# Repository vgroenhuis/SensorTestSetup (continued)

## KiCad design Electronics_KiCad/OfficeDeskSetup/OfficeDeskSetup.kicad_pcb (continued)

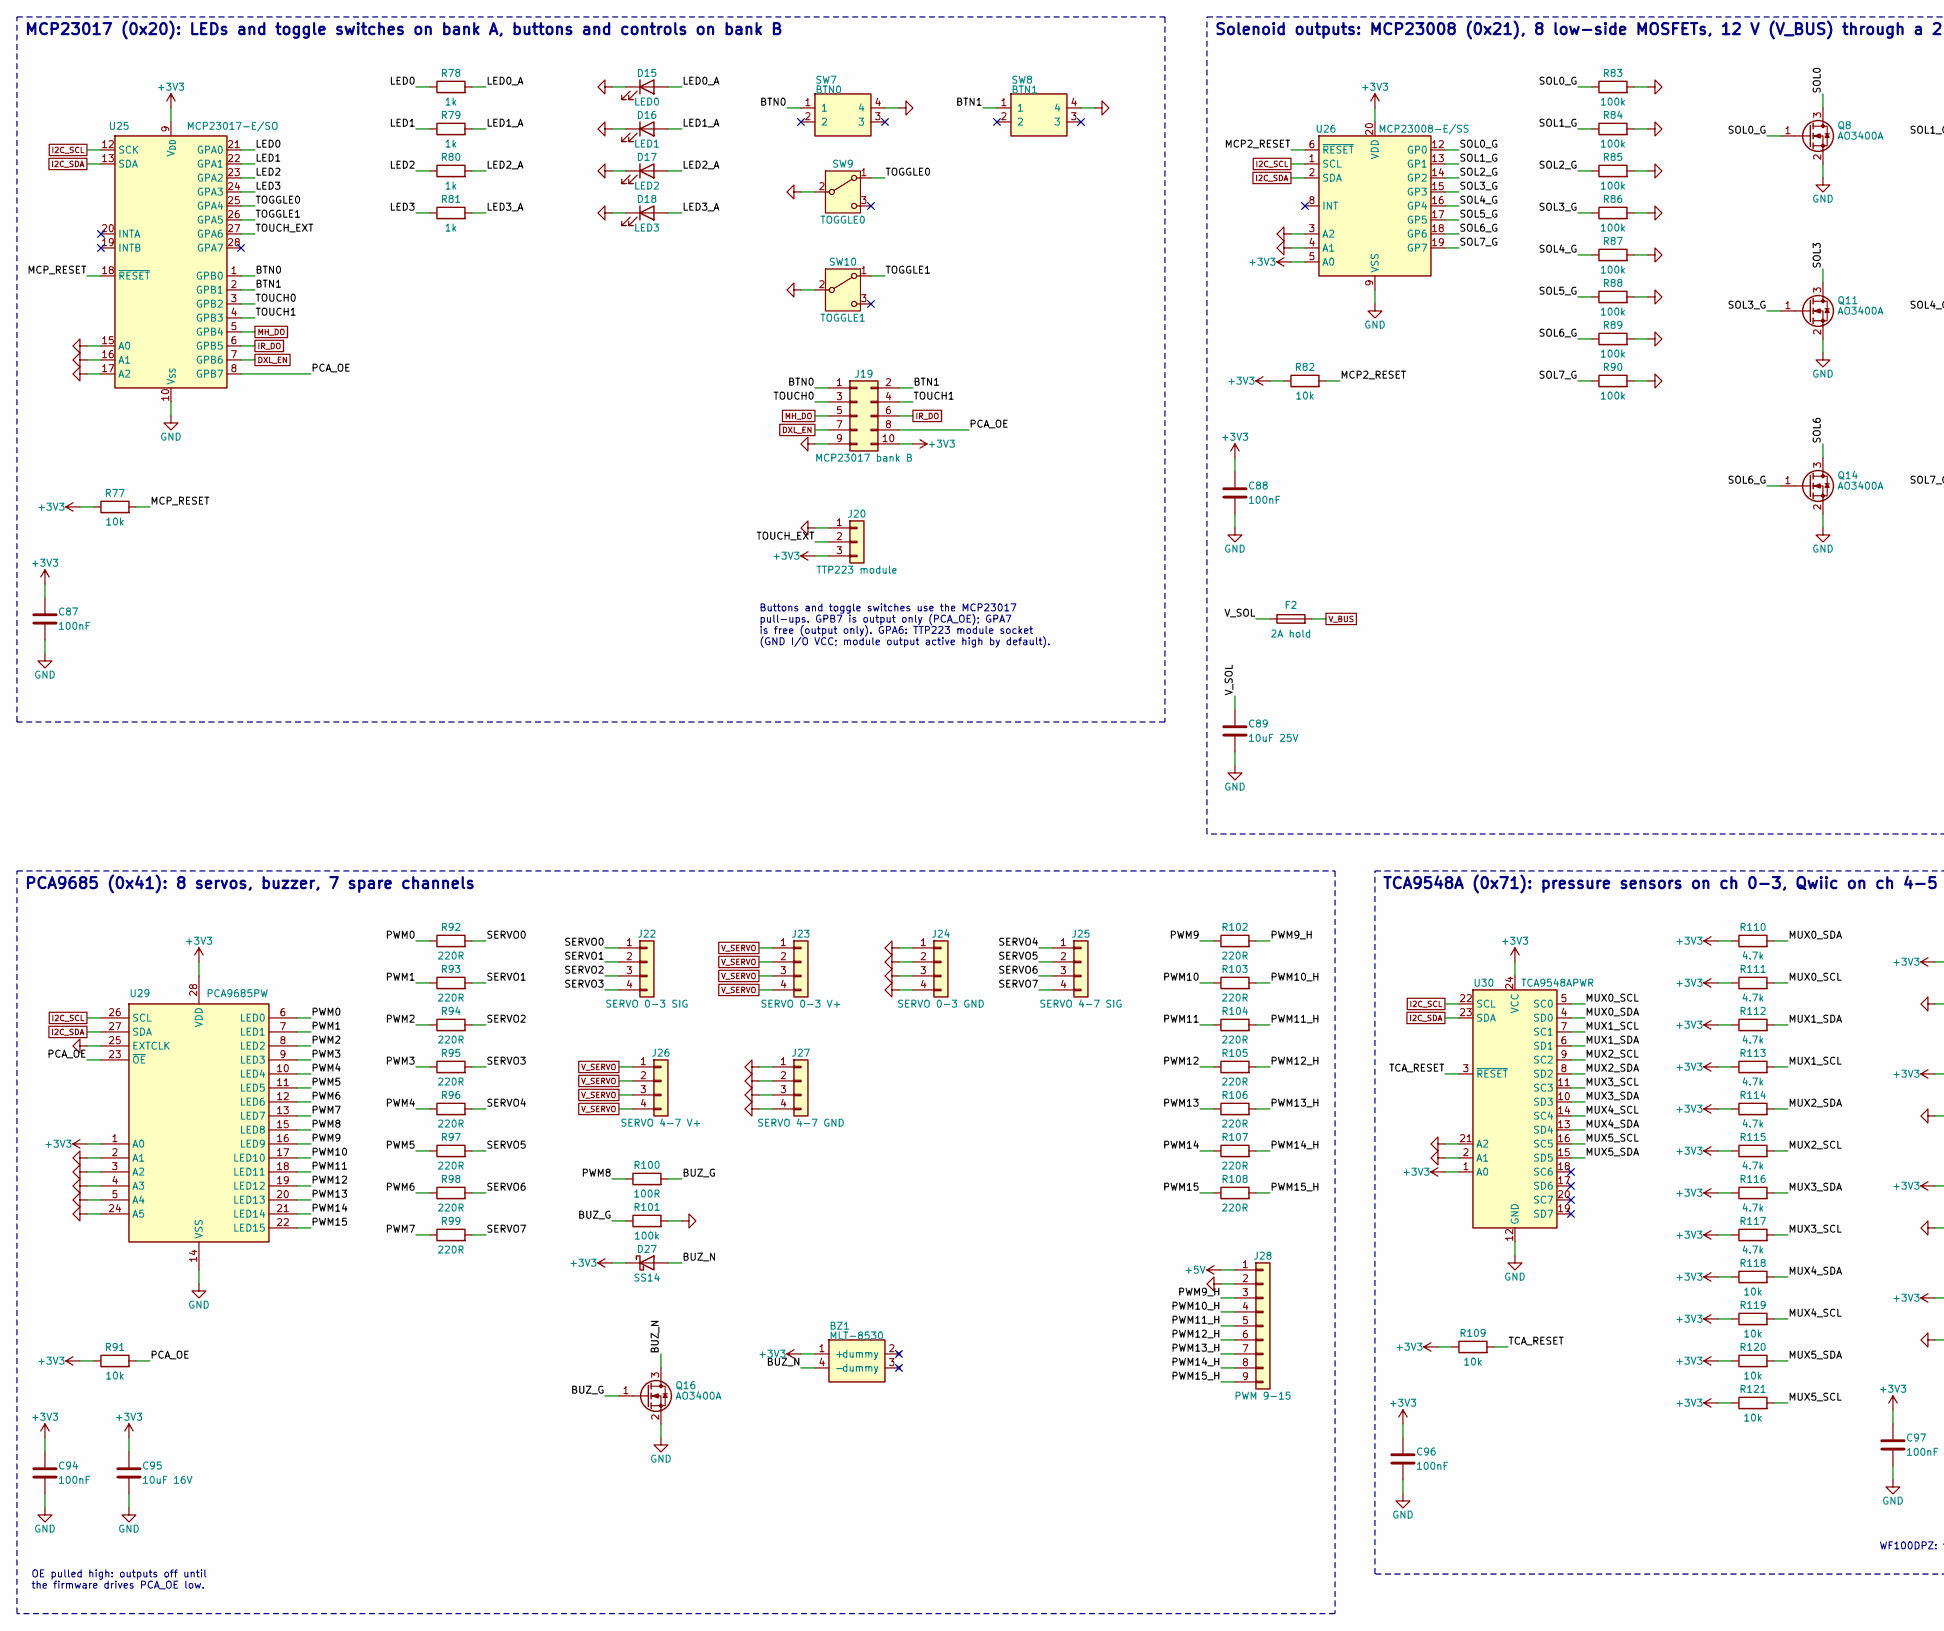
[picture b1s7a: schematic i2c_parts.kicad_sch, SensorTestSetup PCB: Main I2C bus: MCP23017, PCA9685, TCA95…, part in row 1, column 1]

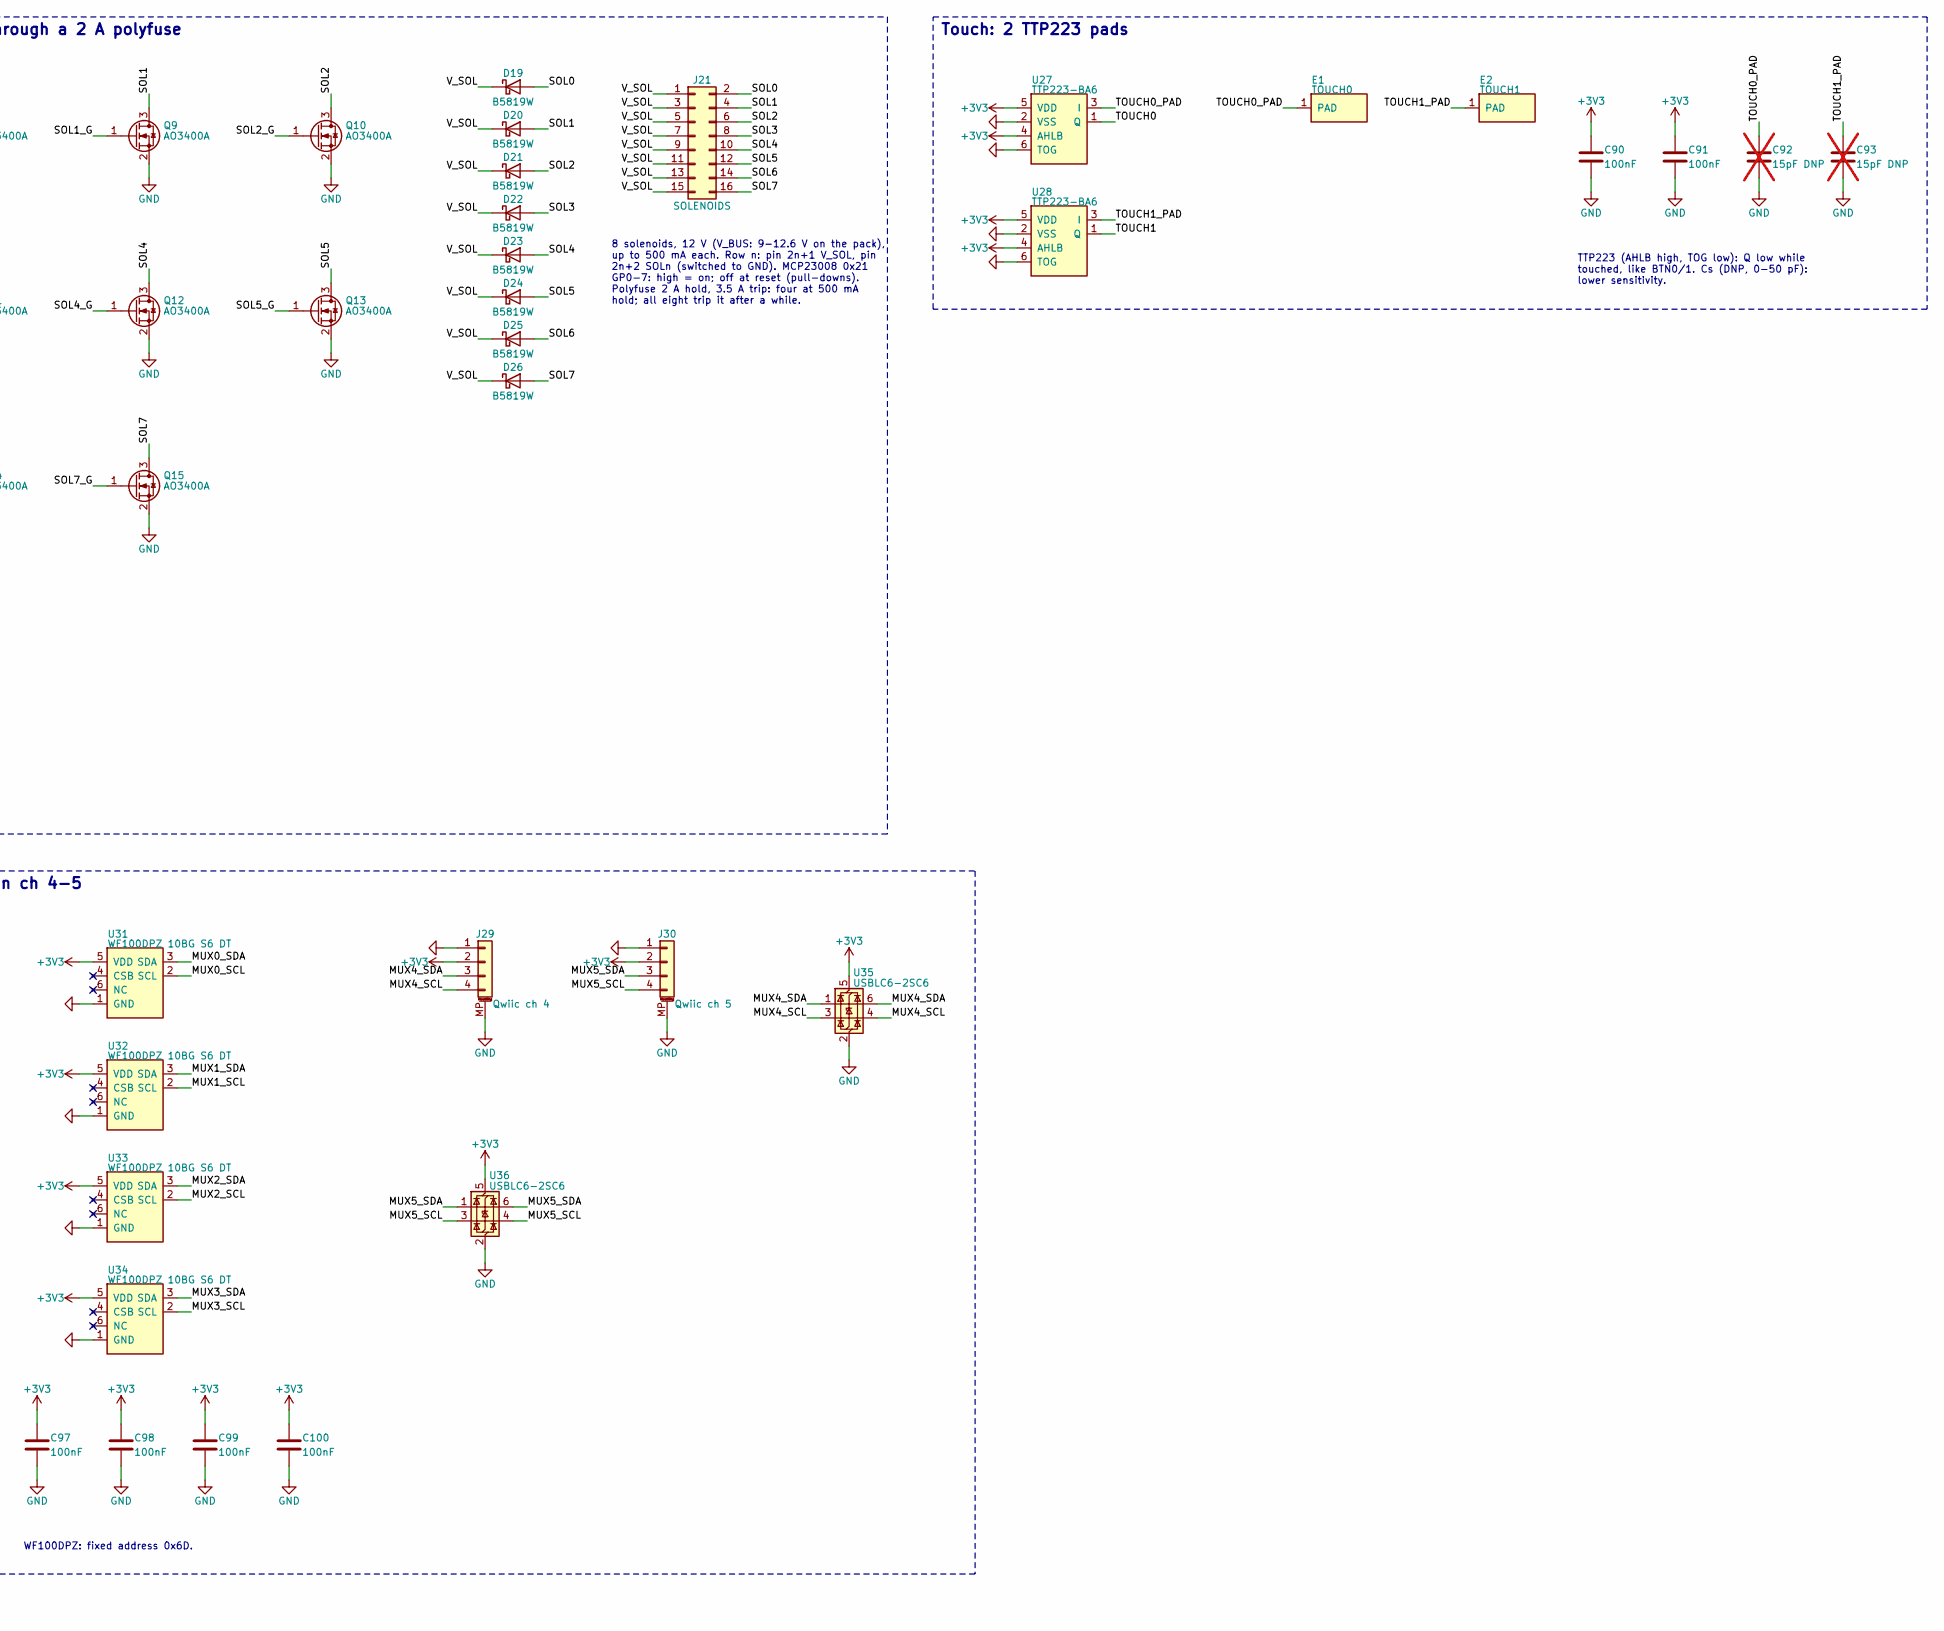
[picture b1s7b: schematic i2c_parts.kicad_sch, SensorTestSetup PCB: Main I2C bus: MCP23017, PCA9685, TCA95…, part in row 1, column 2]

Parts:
BZ1: MLT-8530; BUZ-SMD_4P-L8.5-W8.5-P8.50-BR; LCSC C94599
C87, C88, C90, C91, C94, C96, C97, C98, C99, C100: 100nF; C_0603_1608Metric; LCSC C14663
C89: 10uF 25V; C_1206_3216Metric; LCSC C13585
C92, C93: 15pF DNP; C_0603_1608Metric; LCSC C1644; not fitted
C95: 10uF 16V; C_0805_2012Metric; LCSC C15850
D15: LED0; LED_0603_1608Metric; LCSC C2286
D16: LED1; LED_0603_1608Metric; LCSC C2286
D17: LED2; LED_0603_1608Metric; LCSC C2286
D18: LED3; LED_0603_1608Metric; LCSC C2286
D19, D20, D21, D22, D23, D24, D25, D26: B5819W; D_SOD-123; LCSC C8598
D27: SS14; D_SMA; LCSC C2480
E1: TOUCH0; TouchPad_D11mm
E2: TOUCH1; TouchPad_D11mm
F2: 2A hold; Fuse_1812_4532Metric; LCSC C545213
J19: MCP23017 bank B; PinHeader_2x05_P2.54mm_Vertical; LCSC C32713278
J20: TTP223 module; PinSocket_1x03_P2.54mm_Vertical
J21: SOLENOIDS; PinHeader_2x08_P2.54mm_Vertical
J22: SERVO 0-3 SIG; PinHeader_1x04_P2.54mm_Vertical; LCSC C42431808
J23: SERVO 0-3 V+; PinHeader_1x04_P2.54mm_Vertical; LCSC C42431808
J24: SERVO 0-3 GND; PinHeader_1x04_P2.54mm_Vertical; LCSC C42431808
J25: SERVO 4-7 SIG; PinHeader_1x04_P2.54mm_Vertical; LCSC C42431808
J26: SERVO 4-7 V+; PinHeader_1x04_P2.54mm_Vertical; LCSC C42431808
J27: SERVO 4-7 GND; PinHeader_1x04_P2.54mm_Vertical; LCSC C42431808
J28: PWM 9-15; PinHeader_1x09_P2.54mm_Vertical; LCSC C27985193
J29: Qwiic ch 4; JST_SH_SM04B-SRSS-TB_1x04-1MP_P1.00mm_Horizontal; LCSC C51940130
J30: Qwiic ch 5; JST_SH_SM04B-SRSS-TB_1x04-1MP_P1.00mm_Horizontal; LCSC C51940130
Q8, Q9, Q10, Q11, Q12, Q13, Q14, Q15, Q16: AO3400A; SOT-23; LCSC C20917
R77, R82, R91, R109, R118, R119, R120, R121: 10k; R_0603_1608Metric; LCSC C25804
R78, R79, R80, R81: 1k; R_0603_1608Metric; LCSC C21190
R83, R84, R85, R86, R87, R88, R89, R90, R101: 100k; R_0603_1608Metric; LCSC C25803
R92, R93, R94, R95, R96, R97, R98, R99, R102, R103, R104, R105, R106, R107, R108: 220R; R_0603_1608Metric; LCSC C22962
R100: 100R; R_0603_1608Metric; LCSC C22775
R110, R111, R112, R113, R114, R115, R116, R117: 4.7k; R_0603_1608Metric; LCSC C23162
SW7: BTN0; KEY-TH_4P-L12.0-W12.0-P5.00-LS13.4-EH; LCSC C84931
SW8: BTN1; KEY-TH_4P-L12.0-W12.0-P5.00-LS13.4-EH; LCSC C84931
SW9: TOGGLE0; SW-TH_2MS1T1B1M1QES-5; LCSC C496169
SW10: TOGGLE1; SW-TH_2MS1T1B1M1QES-5; LCSC C496169
U25: MCP23017-E/SO; SOIC-28W_7.5x17.9mm_P1.27mm; LCSC C47023
U26: MCP23008-E/SS; SSOP-20_5.3x7.2mm_P0.65mm; LCSC C148011
U27, U28: TTP223-BA6; SOT-23-6; LCSC C80757
U29: PCA9685PW; TSSOP-28_4.4x9.7mm_P0.65mm; LCSC C2678753
U30: TCA9548APWR; TSSOP-24_4.4x7.8mm_P0.65mm; LCSC C130026
U31, U32, U33, U34: WF100DPZ 10BG S6 DT; SOP-6_L7.0-W7.0-P2.54-LS10.3-TL; LCSC C22388673
U35, U36: USBLC6-2SC6; SOT-23-6; LCSC C2827654

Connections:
+3V3: BZ1.1 (+), C87.1, C88.1, C90.1, C91.1, C94.1, C95.1, C96.1, C97.1, C98.1, C99.1, C100.1, D27.1 (K), J19.10, J20.3, J29.2, J30.2, R77.1, R82.1, R91.1, R109.1, R110.1, R111.1, R112.1, R113.1, R114.1, R115.1, R116.1, R117.1, R118.1, R119.1, R120.1, R121.1, U25.9 (V_{DD}), U26.5 (A0), U26.20 (VDD), U27.4 (AHLB), U27.5 (VDD), U28.4 (AHLB), U28.5 (VDD), U29.1 (A0), U29.28 (VDD), U30.1 (A0), U30.24 (VCC), U31.5 (VDD), U32.5 (VDD), U33.5 (VDD), U34.5 (VDD), U35.5 (VBUS), U36.5 (VBUS); also elsewhere on the board
+5V: J28.1; also elsewhere on the board
/6 Main I2C bus: MCP23017, PCA9685, TCA9548 with pressure sensors/BTN0: J19.1, SW7.1, U25.1 (GPB0)
/6 Main I2C bus: MCP23017, PCA9685, TCA9548 with pressure sensors/BTN1: J19.2, SW8.1, U25.2 (GPB1)
/6 Main I2C bus: MCP23017, PCA9685, TCA9548 with pressure sensors/BUZ_G: Q16.1 (G), R100.2, R101.1
/6 Main I2C bus: MCP23017, PCA9685, TCA9548 with pressure sensors/BUZ_N: BZ1.4 (-), D27.2 (A), Q16.3 (D)
/6 Main I2C bus: MCP23017, PCA9685, TCA9548 with pressure sensors/LED0: R78.1, U25.21 (GPA0)
/6 Main I2C bus: MCP23017, PCA9685, TCA9548 with pressure sensors/LED0_A: D15.2 (A), R78.2
/6 Main I2C bus: MCP23017, PCA9685, TCA9548 with pressure sensors/LED1: R79.1, U25.22 (GPA1)
/6 Main I2C bus: MCP23017, PCA9685, TCA9548 with pressure sensors/LED1_A: D16.2 (A), R79.2
/6 Main I2C bus: MCP23017, PCA9685, TCA9548 with pressure sensors/LED2: R80.1, U25.23 (GPA2)
/6 Main I2C bus: MCP23017, PCA9685, TCA9548 with pressure sensors/LED2_A: D17.2 (A), R80.2
/6 Main I2C bus: MCP23017, PCA9685, TCA9548 with pressure sensors/LED3: R81.1, U25.24 (GPA3)
/6 Main I2C bus: MCP23017, PCA9685, TCA9548 with pressure sensors/LED3_A: D18.2 (A), R81.2
/6 Main I2C bus: MCP23017, PCA9685, TCA9548 with pressure sensors/MCP2_RESET: R82.2, U26.6 (~RESET)
/6 Main I2C bus: MCP23017, PCA9685, TCA9548 with pressure sensors/MCP_RESET: R77.2, U25.18 (~RESET)
/6 Main I2C bus: MCP23017, PCA9685, TCA9548 with pressure sensors/MUX0_SCL: R111.2, U30.5 (SC0), U31.2 (SCL)
/6 Main I2C bus: MCP23017, PCA9685, TCA9548 with pressure sensors/MUX0_SDA: R110.2, U30.4 (SD0), U31.3 (SDA)
/6 Main I2C bus: MCP23017, PCA9685, TCA9548 with pressure sensors/MUX1_SCL: R113.2, U30.7 (SC1), U32.2 (SCL)
/6 Main I2C bus: MCP23017, PCA9685, TCA9548 with pressure sensors/MUX1_SDA: R112.2, U30.6 (SD1), U32.3 (SDA)
/6 Main I2C bus: MCP23017, PCA9685, TCA9548 with pressure sensors/MUX2_SCL: R115.2, U30.9 (SC2), U33.2 (SCL)
/6 Main I2C bus: MCP23017, PCA9685, TCA9548 with pressure sensors/MUX2_SDA: R114.2, U30.8 (SD2), U33.3 (SDA)
/6 Main I2C bus: MCP23017, PCA9685, TCA9548 with pressure sensors/MUX3_SCL: R117.2, U30.11 (SC3), U34.2 (SCL)
/6 Main I2C bus: MCP23017, PCA9685, TCA9548 with pressure sensors/MUX3_SDA: R116.2, U30.10 (SD3), U34.3 (SDA)
/6 Main I2C bus: MCP23017, PCA9685, TCA9548 with pressure sensors/MUX4_SCL: J29.4, R119.2, U30.14 (SC4), U35.3 (I/O2), U35.4 (I/O2)
/6 Main I2C bus: MCP23017, PCA9685, TCA9548 with pressure sensors/MUX4_SDA: J29.3, R118.2, U30.13 (SD4), U35.1 (I/O1), U35.6 (I/O1)
/6 Main I2C bus: MCP23017, PCA9685, TCA9548 with pressure sensors/MUX5_SCL: J30.4, R121.2, U30.16 (SC5), U36.3 (I/O2), U36.4 (I/O2)
/6 Main I2C bus: MCP23017, PCA9685, TCA9548 with pressure sensors/MUX5_SDA: J30.3, R120.2, U30.15 (SD5), U36.1 (I/O1), U36.6 (I/O1)
/6 Main I2C bus: MCP23017, PCA9685, TCA9548 with pressure sensors/PCA_OE: J19.8, R91.2, U25.8 (GPB7), U29.23 (~OE)
/6 Main I2C bus: MCP23017, PCA9685, TCA9548 with pressure sensors/PWM0: R92.1, U29.6 (LED0)
/6 Main I2C bus: MCP23017, PCA9685, TCA9548 with pressure sensors/PWM1: R93.1, U29.7 (LED1)
/6 Main I2C bus: MCP23017, PCA9685, TCA9548 with pressure sensors/PWM2: R94.1, U29.8 (LED2)
/6 Main I2C bus: MCP23017, PCA9685, TCA9548 with pressure sensors/PWM3: R95.1, U29.9 (LED3)
/6 Main I2C bus: MCP23017, PCA9685, TCA9548 with pressure sensors/PWM4: R96.1, U29.10 (LED4)
/6 Main I2C bus: MCP23017, PCA9685, TCA9548 with pressure sensors/PWM5: R97.1, U29.11 (LED5)
/6 Main I2C bus: MCP23017, PCA9685, TCA9548 with pressure sensors/PWM6: R98.1, U29.12 (LED6)
/6 Main I2C bus: MCP23017, PCA9685, TCA9548 with pressure sensors/PWM7: R99.1, U29.13 (LED7)
/6 Main I2C bus: MCP23017, PCA9685, TCA9548 with pressure sensors/PWM8: R100.1, U29.15 (LED8)
/6 Main I2C bus: MCP23017, PCA9685, TCA9548 with pressure sensors/PWM9: R102.1, U29.16 (LED9)
/6 Main I2C bus: MCP23017, PCA9685, TCA9548 with pressure sensors/PWM9_H: J28.3, R102.2
/6 Main I2C bus: MCP23017, PCA9685, TCA9548 with pressure sensors/PWM10: R103.1, U29.17 (LED10)
/6 Main I2C bus: MCP23017, PCA9685, TCA9548 with pressure sensors/PWM10_H: J28.4, R103.2
/6 Main I2C bus: MCP23017, PCA9685, TCA9548 with pressure sensors/PWM11: R104.1, U29.18 (LED11)
/6 Main I2C bus: MCP23017, PCA9685, TCA9548 with pressure sensors/PWM11_H: J28.5, R104.2
/6 Main I2C bus: MCP23017, PCA9685, TCA9548 with pressure sensors/PWM12: R105.1, U29.19 (LED12)
/6 Main I2C bus: MCP23017, PCA9685, TCA9548 with pressure sensors/PWM12_H: J28.6, R105.2
/6 Main I2C bus: MCP23017, PCA9685, TCA9548 with pressure sensors/PWM13: R106.1, U29.20 (LED13)
/6 Main I2C bus: MCP23017, PCA9685, TCA9548 with pressure sensors/PWM13_H: J28.7, R106.2
/6 Main I2C bus: MCP23017, PCA9685, TCA9548 with pressure sensors/PWM14: R107.1, U29.21 (LED14)
/6 Main I2C bus: MCP23017, PCA9685, TCA9548 with pressure sensors/PWM14_H: J28.8, R107.2
/6 Main I2C bus: MCP23017, PCA9685, TCA9548 with pressure sensors/PWM15: R108.1, U29.22 (LED15)
/6 Main I2C bus: MCP23017, PCA9685, TCA9548 with pressure sensors/PWM15_H: J28.9, R108.2
/6 Main I2C bus: MCP23017, PCA9685, TCA9548 with pressure sensors/SERVO0: J22.1, R92.2
/6 Main I2C bus: MCP23017, PCA9685, TCA9548 with pressure sensors/SERVO1: J22.2, R93.2
/6 Main I2C bus: MCP23017, PCA9685, TCA9548 with pressure sensors/SERVO2: J22.3, R94.2
/6 Main I2C bus: MCP23017, PCA9685, TCA9548 with pressure sensors/SERVO3: J22.4, R95.2
/6 Main I2C bus: MCP23017, PCA9685, TCA9548 with pressure sensors/SERVO4: J25.1, R96.2
/6 Main I2C bus: MCP23017, PCA9685, TCA9548 with pressure sensors/SERVO5: J25.2, R97.2
/6 Main I2C bus: MCP23017, PCA9685, TCA9548 with pressure sensors/SERVO6: J25.3, R98.2
/6 Main I2C bus: MCP23017, PCA9685, TCA9548 with pressure sensors/SERVO7: J25.4, R99.2
/6 Main I2C bus: MCP23017, PCA9685, TCA9548 with pressure sensors/SOL0: D19.2 (A), J21.2, Q8.3 (D)
/6 Main I2C bus: MCP23017, PCA9685, TCA9548 with pressure sensors/SOL0_G: Q8.1 (G), R83.1, U26.12 (GP0)
/6 Main I2C bus: MCP23017, PCA9685, TCA9548 with pressure sensors/SOL1: D20.2 (A), J21.4, Q9.3 (D)
/6 Main I2C bus: MCP23017, PCA9685, TCA9548 with pressure sensors/SOL1_G: Q9.1 (G), R84.1, U26.13 (GP1)
/6 Main I2C bus: MCP23017, PCA9685, TCA9548 with pressure sensors/SOL2: D21.2 (A), J21.6, Q10.3 (D)
/6 Main I2C bus: MCP23017, PCA9685, TCA9548 with pressure sensors/SOL2_G: Q10.1 (G), R85.1, U26.14 (GP2)
/6 Main I2C bus: MCP23017, PCA9685, TCA9548 with pressure sensors/SOL3: D22.2 (A), J21.8, Q11.3 (D)
/6 Main I2C bus: MCP23017, PCA9685, TCA9548 with pressure sensors/SOL3_G: Q11.1 (G), R86.1, U26.15 (GP3)
/6 Main I2C bus: MCP23017, PCA9685, TCA9548 with pressure sensors/SOL4: D23.2 (A), J21.10, Q12.3 (D)
/6 Main I2C bus: MCP23017, PCA9685, TCA9548 with pressure sensors/SOL4_G: Q12.1 (G), R87.1, U26.16 (GP4)
/6 Main I2C bus: MCP23017, PCA9685, TCA9548 with pressure sensors/SOL5: D24.2 (A), J21.12, Q13.3 (D)
/6 Main I2C bus: MCP23017, PCA9685, TCA9548 with pressure sensors/SOL5_G: Q13.1 (G), R88.1, U26.17 (GP5)
/6 Main I2C bus: MCP23017, PCA9685, TCA9548 with pressure sensors/SOL6: D25.2 (A), J21.14, Q14.3 (D)
/6 Main I2C bus: MCP23017, PCA9685, TCA9548 with pressure sensors/SOL6_G: Q14.1 (G), R89.1, U26.18 (GP6)
/6 Main I2C bus: MCP23017, PCA9685, TCA9548 with pressure sensors/SOL7: D26.2 (A), J21.16, Q15.3 (D)
/6 Main I2C bus: MCP23017, PCA9685, TCA9548 with pressure sensors/SOL7_G: Q15.1 (G), R90.1, U26.19 (GP7)
/6 Main I2C bus: MCP23017, PCA9685, TCA9548 with pressure sensors/TCA_RESET: R109.2, U30.3 (~RESET)
/6 Main I2C bus: MCP23017, PCA9685, TCA9548 with pressure sensors/TOGGLE0: SW9.1 (A), U25.25 (GPA4)
/6 Main I2C bus: MCP23017, PCA9685, TCA9548 with pressure sensors/TOGGLE1: SW10.1 (A), U25.26 (GPA5)
/6 Main I2C bus: MCP23017, PCA9685, TCA9548 with pressure sensors/TOUCH0: J19.3, U25.3 (GPB2), U27.1 (Q)
/6 Main I2C bus: MCP23017, PCA9685, TCA9548 with pressure sensors/TOUCH0_PAD: C92.1, E1.1, U27.3 (I)
/6 Main I2C bus: MCP23017, PCA9685, TCA9548 with pressure sensors/TOUCH1: J19.4, U25.4 (GPB3), U28.1 (Q)
/6 Main I2C bus: MCP23017, PCA9685, TCA9548 with pressure sensors/TOUCH1_PAD: C93.1, E2.1, U28.3 (I)
/6 Main I2C bus: MCP23017, PCA9685, TCA9548 with pressure sensors/TOUCH_EXT: J20.2, U25.27 (GPA6)
/6 Main I2C bus: MCP23017, PCA9685, TCA9548 with pressure sensors/V_SOL: C89.1, D19.1 (K), D20.1 (K), D21.1 (K), D22.1 (K), D23.1 (K), D24.1 (K), D25.1 (K), D26.1 (K), F2.1, J21.1, J21.3, J21.5, J21.7, J21.9, J21.11, J21.13, J21.15
DXL_EN: J19.7, U25.7 (GPB6); also elsewhere on the board
GND: C87.2, C88.2, C89.2, C90.2, C91.2, C92.2, C93.2, C94.2, C95.2, C96.2, C97.2, C98.2, C99.2, C100.2, D15.1 (K), D16.1 (K), D17.1 (K), D18.1 (K), J19.9, J20.1, J24.1, J24.2, J24.3, J24.4, J27.1, J27.2, J27.3, J27.4, J28.2, J29.1, J29.MP (MountPin), J30.1, J30.MP (MountPin), Q8.2 (S), Q9.2 (S), Q10.2 (S), Q11.2 (S), Q12.2 (S), Q13.2 (S), Q14.2 (S), Q15.2 (S), Q16.2 (S), R83.2, R84.2, R85.2, R86.2, R87.2, R88.2, R89.2, R90.2, R101.2, SW7.4, SW8.4, SW9.2 (B), SW10.2 (B), U25.10 (V_{SS}), U25.15 (A0), U25.16 (A1), U25.17 (A2), U26.3 (A2), U26.4 (A1), U26.9 (VSS), U27.2 (VSS), U27.6 (TOG), U28.2 (VSS), U28.6 (TOG), U29.2 (A1), U29.3 (A2), U29.4 (A3), U29.5 (A4), U29.14 (VSS), U29.24 (A5), U29.25 (EXTCLK), U30.2 (A1), U30.12 (GND), U30.21 (A2), U31.1 (GND), U32.1 (GND), U33.1 (GND), U34.1 (GND), U35.2 (GND), U36.2 (GND); also elsewhere on the board
I2C_SCL: U25.12 (SCK), U26.1 (SCL), U29.26 (SCL), U30.22 (SCL); also elsewhere on the board
I2C_SDA: U25.13 (SDA), U26.2 (SDA), U29.27 (SDA), U30.23 (SDA); also elsewhere on the board
IR_DO: J19.6, U25.6 (GPB5); also elsewhere on the board
MH_DO: J19.5, U25.5 (GPB4); also elsewhere on the board
V_BUS: F2.2; also elsewhere on the board
V_SERVO: J23.1, J23.2, J23.3, J23.4, J26.1, J26.2, J26.3, J26.4; also elsewhere on the board

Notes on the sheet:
Buttons and toggle switches use the MCP23017 pull-ups. GPB7 is output only (PCA_OE); GPA7 is free (output only). GPA6: TTP223 module socket (GND I/O VCC; module output active high by default).
MCP23017 (0x20): LEDs and toggle switches on bank A, buttons and controls on bank B
8 solenoids, 12 V (V_BUS: 9-12.6 V on the pack), up to 500 mA each. Row n: pin 2n+1 V_SOL, pin 2n+2 SOLn (switched to GND). MCP23008 0x21 GP0-7: high = on; off at reset (pull-downs). Polyfuse 2 A hold, 3.5 A trip: four at 500 mA hold; all eight trip it after a while.
Solenoid outputs: MCP23008 (0x21), 8 low-side MOSFETs, 12 V (V_BUS) through a 2 A polyfuse
TTP223 (AHLB high, TOG low): Q low while touched, like BTN0/1. Cs (DNP, 0-50 pF): lower sensitivity.
Touch: 2 TTP223 pads
OE pulled high: outputs off until the firmware drives PCA_OE low.
PCA9685 (0x41): 8 servos, buzzer, 7 spare channels
WF100DPZ: fixed address 0x6D.
TCA9548A (0x71): pressure sensors on ch 0-3, Qwiic on ch 4-5
